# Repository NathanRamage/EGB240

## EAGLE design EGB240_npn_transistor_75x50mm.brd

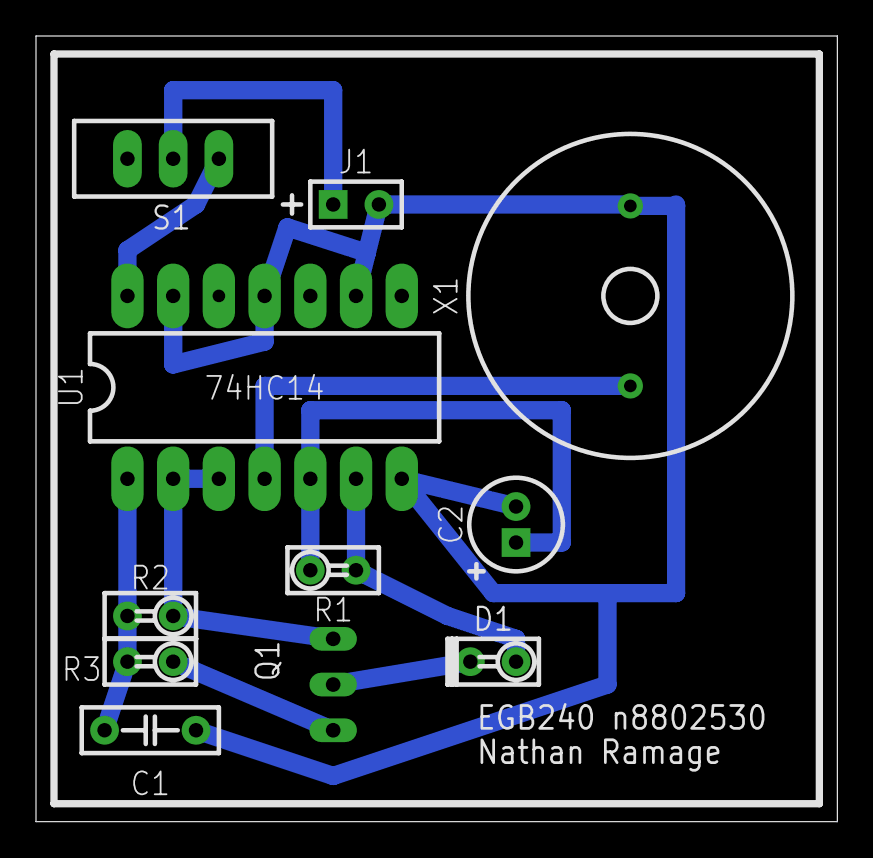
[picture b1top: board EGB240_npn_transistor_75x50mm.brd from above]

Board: 2 copper layers, 44.5 x 43.6 mm, 11 parts (1 on the bottom side), 10 nets.

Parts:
C1: CAP-DISC-P5.08
C2: CAP-RB-P2.0-D5.0
D1: DO35-P2.54
J1: BATT-3V
Q1: PN100; TO92-EBC
R1, R2, R3: AXIAL-P2.54
S1: SS-12
U1: 74HC14; DIP-14
X1: PS1720P02

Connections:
+3V: S1.3, U1.P$14
GND: C1.P$2, C2.P$2, J1.P$2, U1.P$7, U1.P$9, U1.P$11, U1.P$13, X1.P$2
unnamed: C2.P$1, R1.P$2, U1.P$5
unnamed: D1.A, R1.P$1, U1.P$6
unnamed: U1.P$4, X1.P$1
unnamed: D1.K, Q1.B
unnamed: Q1.E, R3.P$2
unnamed: C1.P$1, R2.P$1, R3.P$1, U1.P$1
unnamed: Q1.C, R2.P$2, U1.P$2, U1.P$3
unnamed: J1.P$1, S1.2

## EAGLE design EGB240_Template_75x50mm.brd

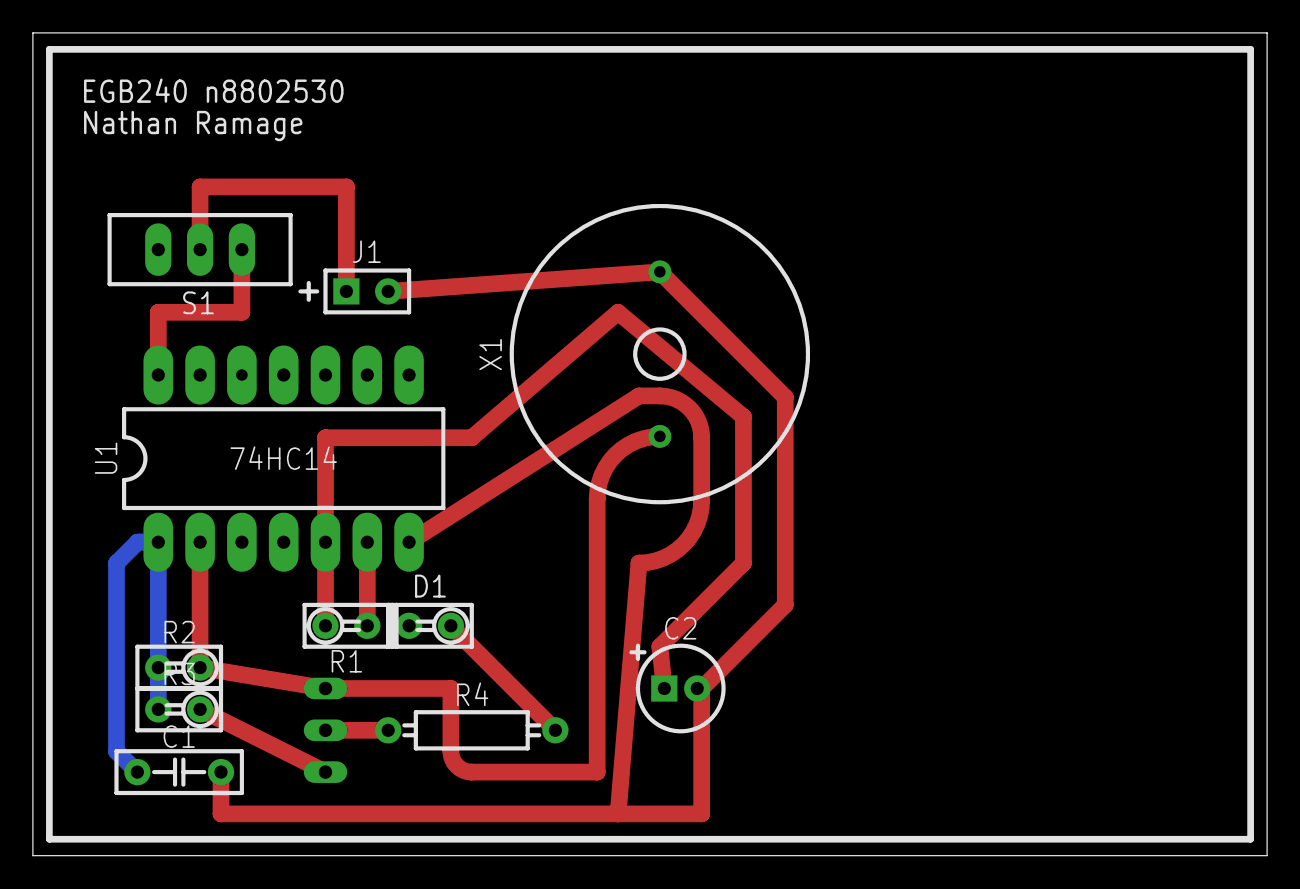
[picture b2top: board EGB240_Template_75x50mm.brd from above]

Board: 2 copper layers, 75.0 x 50.0 mm, 12 parts (1 on the bottom side), 10 nets.

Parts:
C1: CAP-DISC-P5.08
C2: CAP-RB-P2.0-D5.0
D1: DO35-P2.54
J1: BATT-3V
Q1: 2N4126; TO92-CBE
R1, R2, R3: AXIAL-P2.54
R4: AXIAL-P10.16
S1: SS-12
U1: 74HC14; DIP-14
X1: PS1720P02

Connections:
+3V: S1.3, U1.P$14
GND: C1.P$2, C2.P$2, J1.P$2, U1.P$7, X1.P$2
unnamed: C2.P$1, R1.P$2, U1.P$5
unnamed: D1.K, R1.P$1, U1.P$6
unnamed: D1.A, R4.P$2
unnamed: Q1.B, R4.P$1
unnamed: Q1.C, R3.P$2
unnamed: C1.P$1, R2.P$1, R3.P$1, U1.P$1
unnamed: Q1.E, R2.P$2, U1.P$2, X1.P$1
unnamed: J1.P$1, S1.2

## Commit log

2016-03-21 Intitial commit
2016-03-21 Added git ignore file
2016-03-21 unneeded file
2016-03-24 added npn board
2016-03-24 Added Gerber files
2016-03-24 renamed files in zip folders
